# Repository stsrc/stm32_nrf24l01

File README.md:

# stm32_nrf24l01 - GPS localization project

Idea of this project is to create GPS localization system which utilises android
application to present distance and direction to the GPS receiver.

To achieve that multiple devices are used: on slave side we use NEO-6M GPS
module and nrf24l01 module to transmit GPS data to the master side.
On master side we use nrf24l01 to receive GPS data and HM-10 module to send it
to the android phone.

Android application is located in another repository: [whereIsCat](https://github.com/stsrc/whereIsCat)

## Repository content:

slave PCB with nrf24l01 transmitter and NEO-6M GPS receiver, battery powered

    ./src-kicad/stm32_slave_bat

slave firmware

    ./stm32f031f6_slave

master PCB with nrf24l01 receiver and HM-10 bluetooth transmitter, battery powered

    ./src-kicad/stm32_master_bt_bat

master firmware

    ./stm32f031f6_master

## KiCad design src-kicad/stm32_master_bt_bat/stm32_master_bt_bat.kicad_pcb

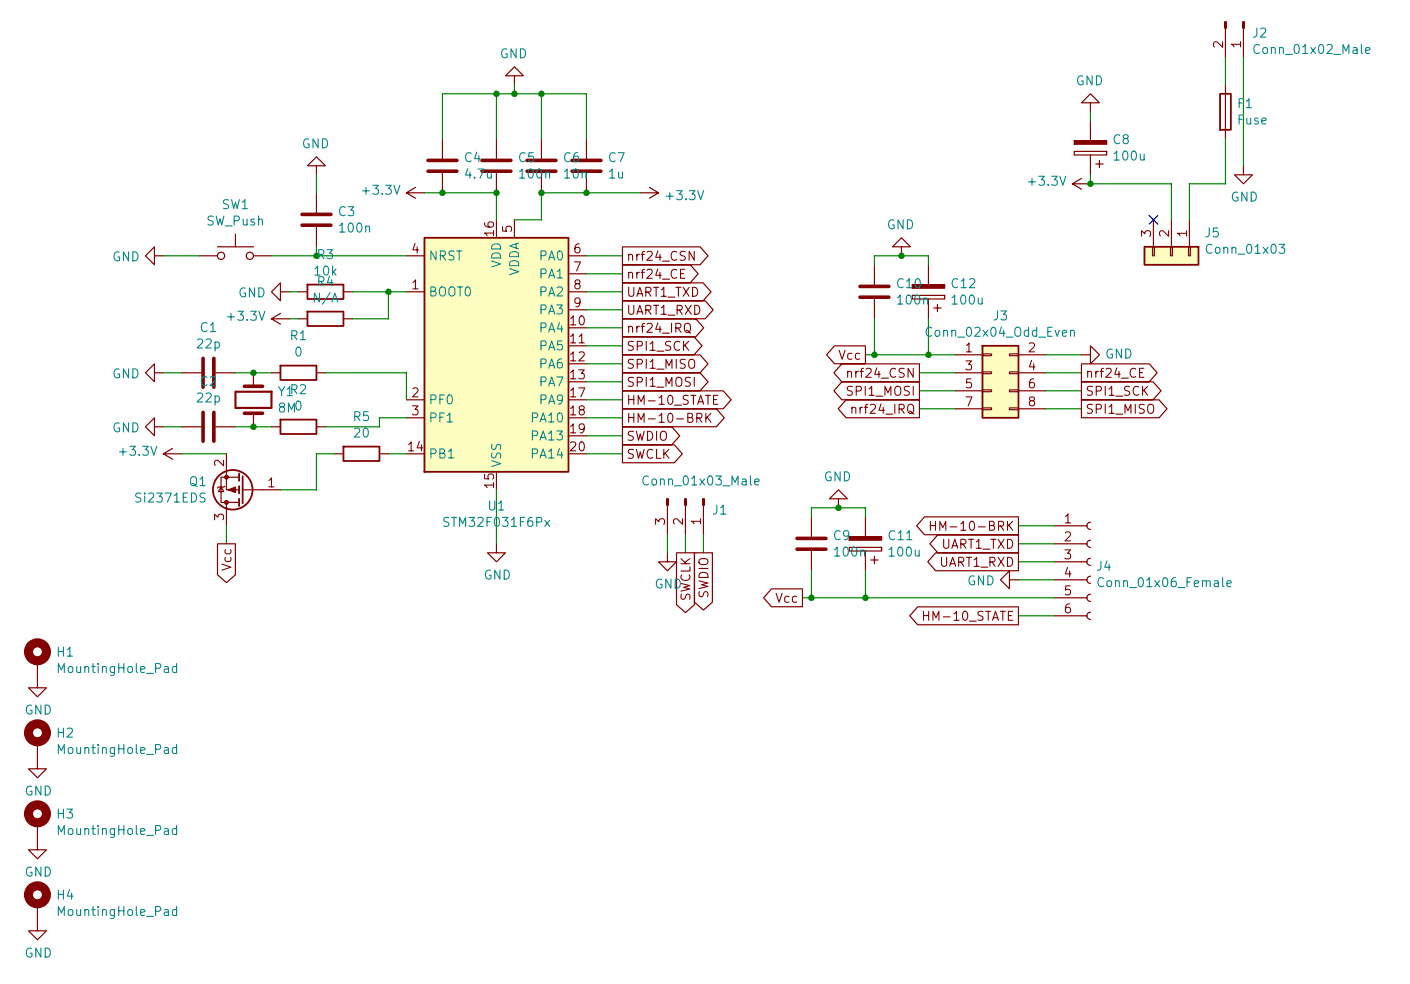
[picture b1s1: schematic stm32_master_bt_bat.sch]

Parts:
C1, C2: 22p; C_0805_2012Metric_Pad1.18x1.45mm_HandSolder
C3, C5, C9, C10: 100n; C_0805_2012Metric_Pad1.18x1.45mm_HandSolder
C4: 4.7u; C_0805_2012Metric_Pad1.18x1.45mm_HandSolder
C6: 10n; C_0805_2012Metric_Pad1.18x1.45mm_HandSolder
C7: 1u; C_0805_2012Metric_Pad1.18x1.45mm_HandSolder
C8, C11, C12: 100u; CP_Elec_6.3x5.8
F1: Fuse; smd-2410
H1, H2, H3, H4: MountingHole_Pad; MountingHole_3.2mm_M3_DIN965_Pad
J1: Conn_01x03_Male; PinHeader_1x03_P2.54mm_Vertical
J2: Conn_01x02_Male; PinHeader_1x02_P2.54mm_Vertical
J3: Conn_02x04_Odd_Even; PinSocket_2x04_P2.54mm_Vertical
J4: Conn_01x06_Female; PinSocket_1x06_P2.54mm_Vertical
J5: Conn_01x03; PRZELBL1X3
Q1: Si2371EDS; SOT-23
R1, R2: 0; R_0805_2012Metric_Pad1.20x1.40mm_HandSolder
R3: 10k; R_0805_2012Metric_Pad1.20x1.40mm_HandSolder
R4: N/A; R_0805_2012Metric_Pad1.20x1.40mm_HandSolder
R5: 20; R_0805_2012Metric_Pad1.20x1.40mm_HandSolder
SW1: SW_Push; SW_PUSH_6mm_H5mm
U1: STM32F031F6Px; TSSOP-20_4.4x6.5mm_P0.65mm
Y1: 8M; Crystal_SMD_HC49-SD

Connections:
+3V3: C4.2, C5.2, C6.1, C7.1, C8.1, J5.2, Q1.2 (S), R4.2, U1.5 (VDDA), U1.16 (VDD)
GND: C1.2, C2.2, C3.1, C4.1, C5.1, C6.2, C7.2, C8.2, C9.1, C10.1, C11.2, C12.2, H1.1, H2.1, H3.1, H4.1, J1.3, J2.1, J3.2, J4.4, R3.2, SW1.1, U1.15 (VSS)
HM-10-BRK: J4.1, U1.18 (PA10)
HM-10_STATE: J4.6, U1.17 (PA9)
unnamed: C1.1, R1.2, Y1.1
unnamed: C2.1, R2.2, Y1.2
unnamed: C3.2, SW1.2, U1.4 (NRST)
unnamed: F1.1, J2.2
unnamed: F1.2, J5.1
unnamed: Q1.1 (G), R5.2
unnamed: R1.1, U1.2 (PF0)
unnamed: R2.1, U1.3 (PF1)
unnamed: R3.1, R4.1, U1.1 (BOOT0)
unnamed: R5.1, U1.14 (PB1)
SPI1_MISO: J3.8, U1.12 (PA6)
SPI1_MOSI: J3.5, U1.13 (PA7)
SPI1_SCK: J3.6, U1.11 (PA5)
SWCLK: J1.2, U1.20 (PA14)
SWDIO: J1.1, U1.19 (PA13)
UART1_RXD: J4.3, U1.9 (PA3)
UART1_TXD: J4.2, U1.8 (PA2)
Vcc: C9.2, C10.2, C11.1, C12.1, J3.1, J4.5, Q1.3 (D)
nrf24_CE: J3.4, U1.7 (PA1)
nrf24_CSN: J3.3, U1.6 (PA0)
nrf24_IRQ: J3.7, U1.10 (PA4)

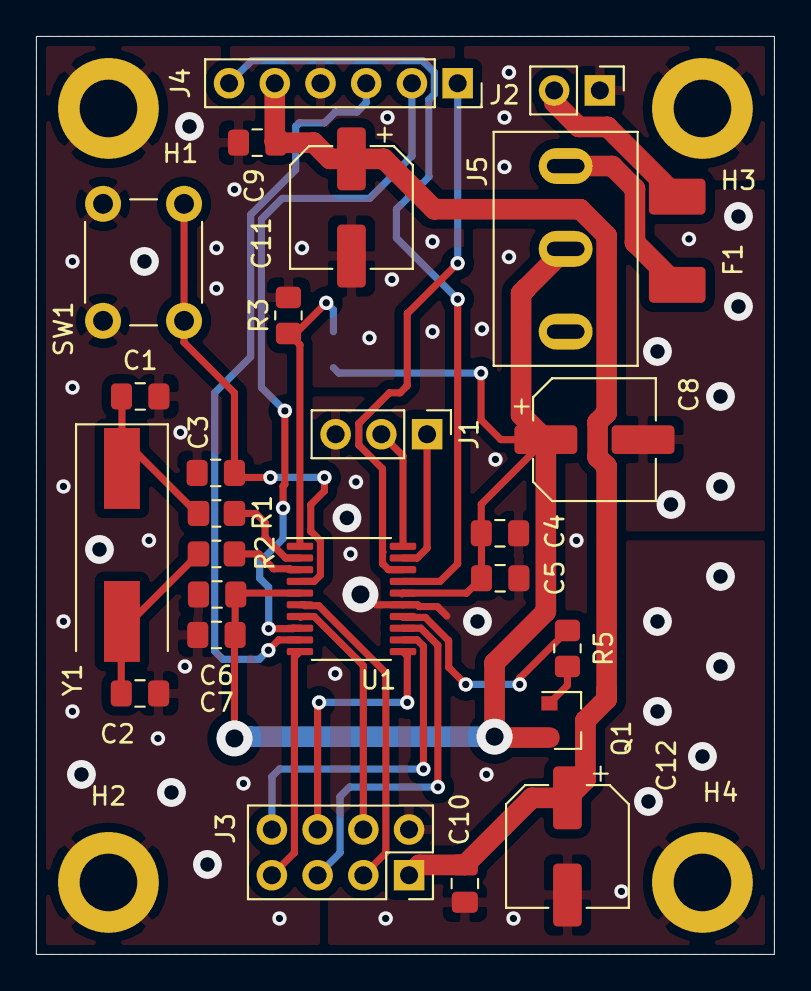
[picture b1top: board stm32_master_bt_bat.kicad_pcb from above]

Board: 2 copper layers, 41.0 x 51.0 mm, 31 parts (1 on the bottom side), 25 nets.

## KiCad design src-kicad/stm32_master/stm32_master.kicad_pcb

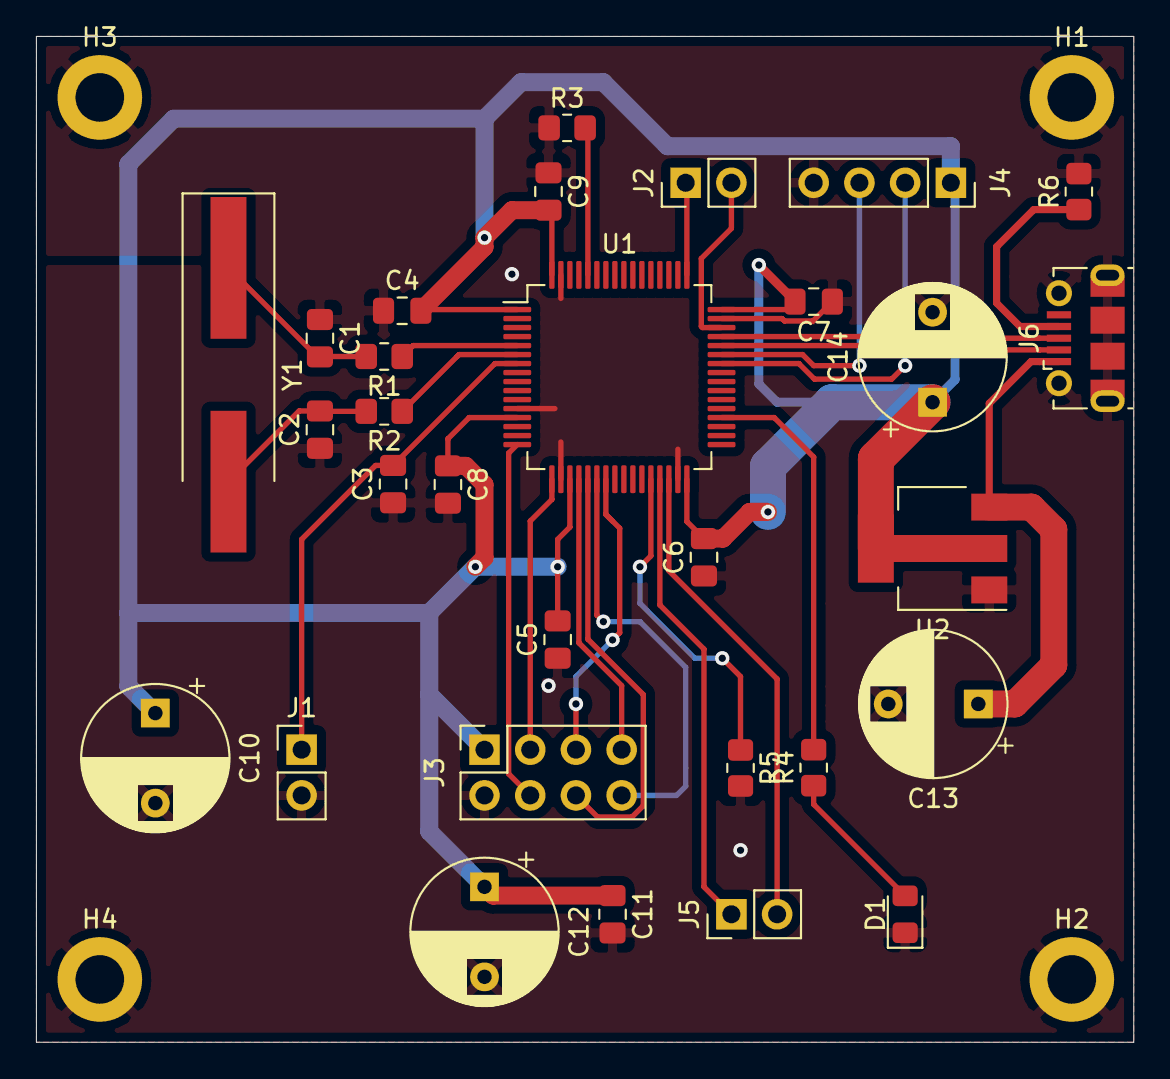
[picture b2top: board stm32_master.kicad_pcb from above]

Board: 2 copper layers, 61.0 x 55.9 mm, 34 parts (0 on the bottom side), 27 nets.

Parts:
C1, C2: 20p; C_0805_2012Metric_Pad1.18x1.45mm_HandSolder
C3, C4, C5, C6, C7, C9, C11: 100n; C_0805_2012Metric_Pad1.18x1.45mm_HandSolder
C8: 10n; C_0805_2012Metric_Pad1.18x1.45mm_HandSolder
C10: 1u; CP_Radial_D8.0mm_P5.00mm
C12, C14: 100u; CP_Radial_D8.0mm_P5.00mm
C13: 10u; CP_Radial_D8.0mm_P5.00mm
D1: LED; LED_0805_2012Metric_Pad1.15x1.40mm_HandSolder
H1, H2, H3, H4: MountingHole_Pad; MountingHole_2.7mm_M2.5_DIN965_Pad
J1, J2, J5: Conn_01x02_Male; PinHeader_1x02_P2.54mm_Vertical
J3: Conn_02x04_Odd_Even; PinSocket_2x04_P2.54mm_Vertical
J4: Conn_01x04; PinSocket_1x04_P2.54mm_Vertical
J6: USB_B_Micro; USB_Micro-B_Molex-105017-0001
R1: 0; R_0805_2012Metric_Pad1.20x1.40mm_HandSolder
R2: 220; R_0805_2012Metric_Pad1.20x1.40mm_HandSolder
R3, R5: 470; R_0805_2012Metric_Pad1.20x1.40mm_HandSolder
R4: 4.75; R_0805_2012Metric_Pad1.20x1.40mm_HandSolder
R6: N/A; R_0805_2012Metric_Pad1.20x1.40mm_HandSolder
U1: STM32F103RBTx; LQFP-64_10x10mm_P0.5mm
U2: LD1117S33TR_SOT223; SOT-223-3_TabPin2
Y1: Crystal; Crystal_SMD_HC49-SD_HandSoldering

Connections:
+3V3: C4.2, C5.2, C6.2, C7.2, C8.1, C9.2, C10.1, C11.1, C12.1, C14.1, J3.1, J4.1, U1.1, U1.13, U1.19, U1.32, U1.48, U1.64, U2.2
+5V: C13.1, J6.1, U2.3
BOOT1: R5.1, U1.28
GND: C1.1, C2.1, C3.1, C4.1, C5.1, C6.1, C7.1, C8.2, C9.1, C10.2, C11.2, C12.2, C13.2, C14.2, D1.1, H1.1, H2.1, H3.1, H4.1, J1.2, J3.2, J4.4, J6.5, J6.6, R3.1, R5.2, R6.2, U1.12, U1.18, U1.31, U1.47, U1.63, U2.1
unnamed: C1.2, R1.2, Y1.1
unnamed: C2.2, R2.2, Y1.2
unnamed: C3.2, J1.1, U1.7
unnamed: D1.2, R4.1
unnamed: J6.4, R6.1
unnamed: R1.1, U1.5
unnamed: R2.1, U1.6
unnamed: R3.2, U1.60
unnamed: R4.2, U1.36
SPI1_MISO: J3.8, U1.22
SPI1_MOSI: J3.5, U1.23
SPI1_SCK: J3.6, U1.21
SWCLK: J2.1, U1.49
SWDIO: J2.2, U1.46
USART1_RX: J4.3, U1.43
USART1_TX: J4.2, U1.42
USART3_RX: J5.2, U1.30
USART3_TX: J5.1, U1.29
USB_DM: J6.2, U1.44
USB_DP: J6.3, U1.45
nrf24_CE: J3.4, U1.16
nrf24_CSN: J3.3, U1.17
nrf24_IRQ: J3.7, U1.20

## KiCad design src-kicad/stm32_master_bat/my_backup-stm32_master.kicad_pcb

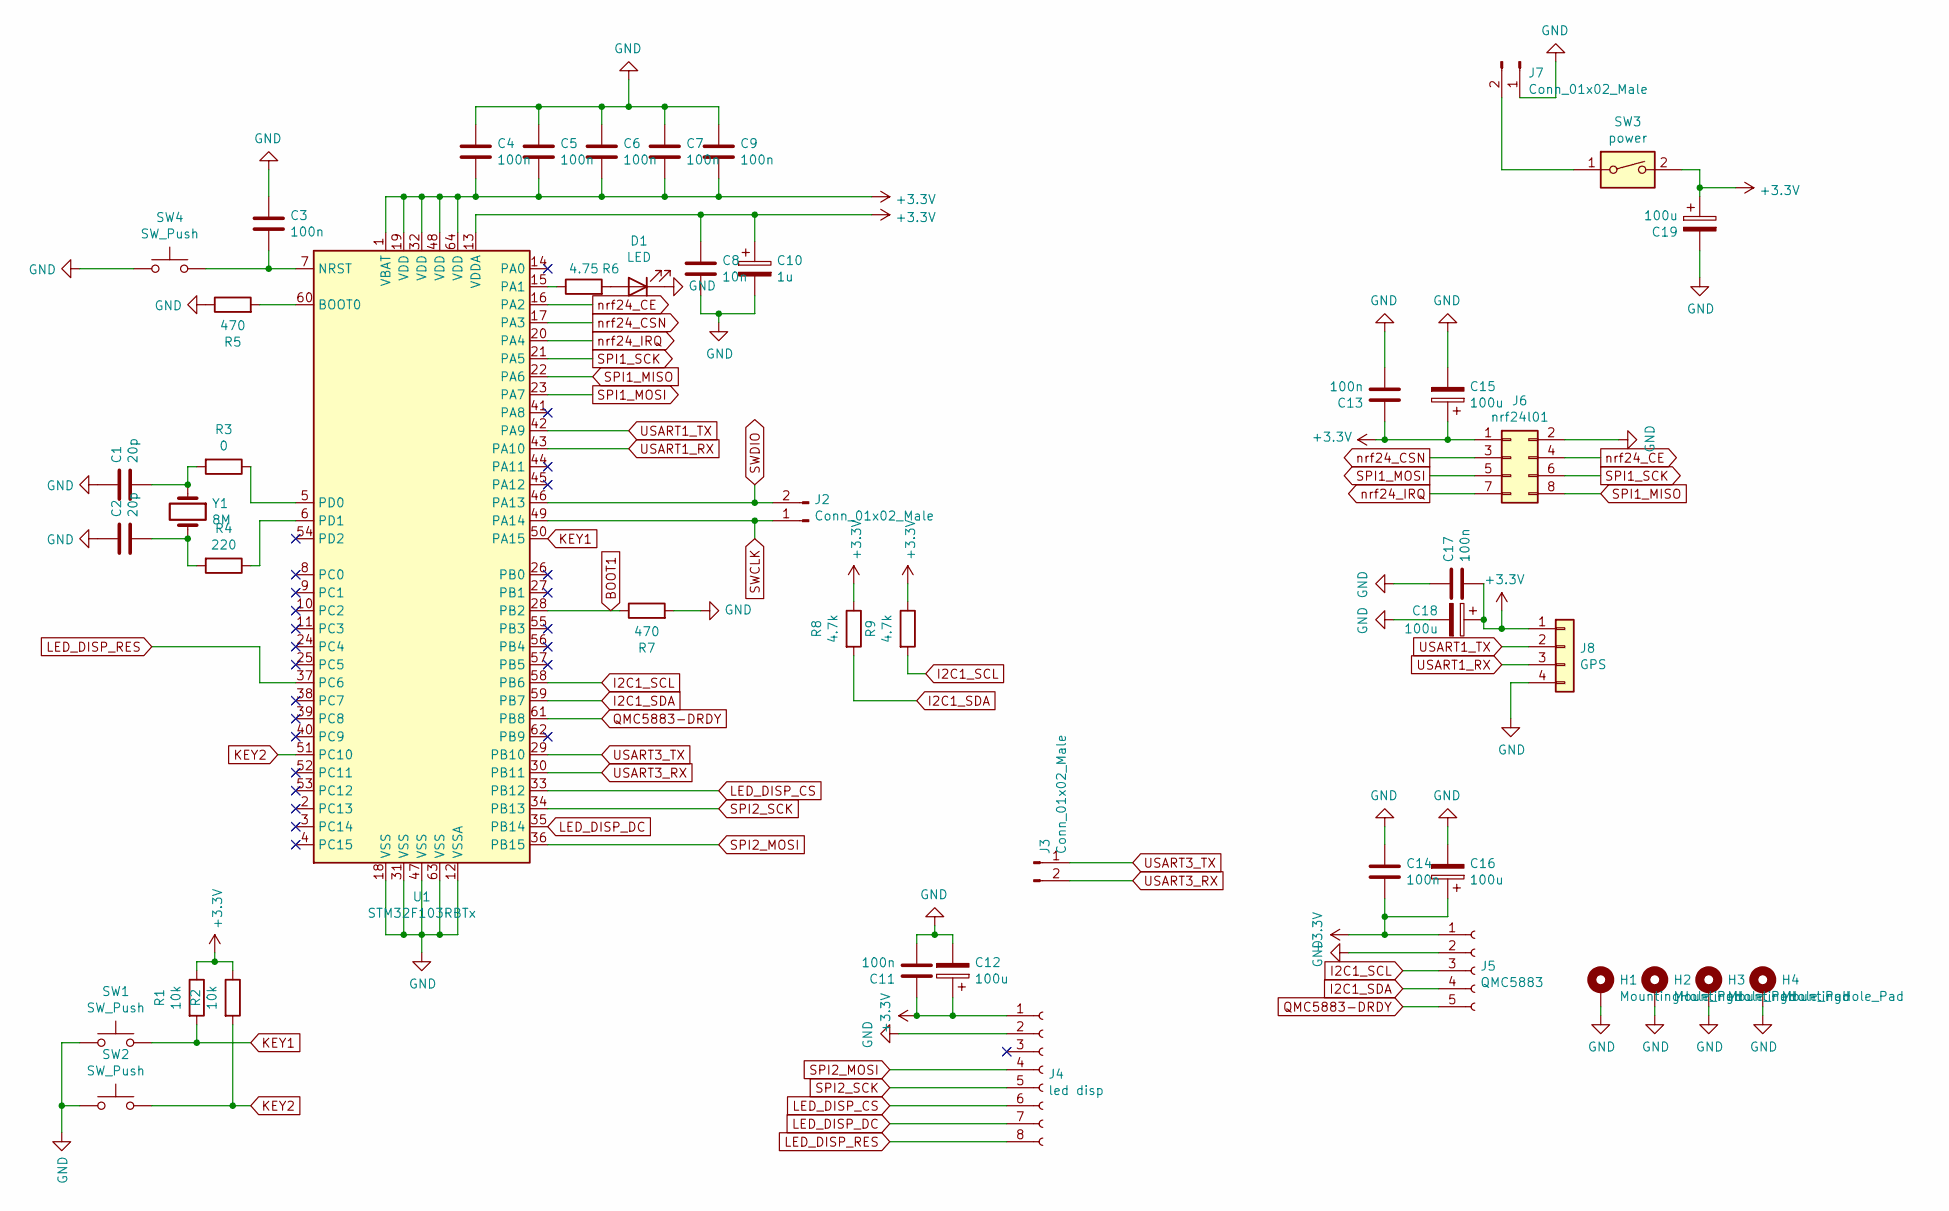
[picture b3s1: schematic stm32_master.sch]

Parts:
C1, C2: 20p; C_0805_2012Metric_Pad1.18x1.45mm_HandSolder
C3, C4, C5, C6, C7, C9, C11, C13, C14, C17: 100n; C_0805_2012Metric_Pad1.18x1.45mm_HandSolder
C8: 10n; C_0805_2012Metric_Pad1.18x1.45mm_HandSolder
C10: 1u; CP_Radial_D5.0mm_P2.50mm
C12, C15, C16, C18, C19: 100u; CP_Radial_D5.0mm_P2.50mm
D1: LED; LED_0805_2012Metric_Pad1.15x1.40mm_HandSolder
H1, H2, H3, H4: MountingHole_Pad; MountingHole_2.7mm_M2.5_DIN965_Pad
J2, J3, J7: Conn_01x02_Male; PinHeader_1x02_P2.54mm_Vertical
J4: led disp; PinSocket_1x08_P2.54mm_Vertical
J5: QMC5883; PinSocket_1x05_P2.54mm_Vertical
J6: nrf24l01; PinSocket_2x04_P2.54mm_Vertical
J8: GPS; PinSocket_1x04_P2.54mm_Vertical
R1, R2: 10k; R_0805_2012Metric_Pad1.20x1.40mm_HandSolder
R3: 0; R_0805_2012Metric_Pad1.20x1.40mm_HandSolder
R4: 220; R_0805_2012Metric_Pad1.20x1.40mm_HandSolder
R5, R7: 470; R_0805_2012Metric_Pad1.20x1.40mm_HandSolder
R6: 4.75; R_0805_2012Metric_Pad1.20x1.40mm_HandSolder
R8, R9: 4.7k; R_0805_2012Metric_Pad1.20x1.40mm_HandSolder
SW1, SW2, SW4: SW_Push; SW_PUSH_6mm_H5mm
SW3: power; SW_DIP_SPSTx01_Slide_6.7x4.1mm_W7.62mm_P2.54mm_LowProfile
U1: STM32F103RBTx; LQFP-64_10x10mm_P0.5mm
Y1: 8M; Crystal_SMD_HC49-SD_HandSoldering

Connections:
+3V3: C4.2, C5.2, C6.2, C7.2, C8.1, C9.2, C10.1, C11.1, C12.1, C13.1, C14.2, C15.1, C16.1, C17.2, C18.1, C19.1, J4.1, J5.1, J6.1, J8.1, R1.1, R2.1, R8.1, R9.1, SW3.2, U1.1 (VBAT), U1.13 (VDDA), U1.19 (VDD), U1.32 (VDD), U1.48 (VDD), U1.64 (VDD)
BOOT1: R7.1, U1.28 (PB2)
GND: C1.1, C2.1, C3.1, C4.1, C5.1, C6.1, C7.1, C8.2, C9.1, C10.2, C11.2, C12.2, C13.2, C14.1, C15.2, C16.2, C17.1, C18.2, C19.2, D1.1 (K), H1.1, H2.1, H3.1, H4.1, J4.2, J5.2, J6.2, J7.1, J8.4, R5.1, R7.2, SW1.1, SW2.1, SW4.1, U1.12 (VSSA), U1.18 (VSS), U1.31 (VSS), U1.47 (VSS), U1.63 (VSS)
I2C1_SCL: J5.3, R9.2, U1.58 (PB6)
I2C1_SDA: J5.4, R8.2, U1.59 (PB7)
KEY1: R1.2, SW1.2, U1.50 (PA15)
KEY2: R2.2, SW2.2, U1.51 (PC10)
LED_DISP_CS: J4.6, U1.33 (PB12)
LED_DISP_DC: J4.7, U1.35 (PB14)
LED_DISP_RES: J4.8, U1.37 (PC6)
unnamed: C1.2, R3.2, Y1.1
unnamed: C2.2, R4.2, Y1.2
unnamed: C3.2, SW4.2, U1.7 (NRST)
unnamed: D1.2 (A), R6.2
unnamed: J7.2, SW3.1
unnamed: R3.1, U1.5 (PD0)
unnamed: R4.1, U1.6 (PD1)
unnamed: R5.2, U1.60 (BOOT0)
unnamed: R6.1, U1.15 (PA1)
QMC5883-DRDY: J5.5, U1.61 (PB8)
SPI1_MISO: J6.8, U1.22 (PA6)
SPI1_MOSI: J6.5, U1.23 (PA7)
SPI1_SCK: J6.6, U1.21 (PA5)
SPI2_MOSI: J4.4, U1.36 (PB15)
SPI2_SCK: J4.5, U1.34 (PB13)
SWCLK: J2.1, U1.49 (PA14)
SWDIO: J2.2, U1.46 (PA13)
USART1_RX: J8.3, U1.43 (PA10)
USART1_TX: J8.2, U1.42 (PA9)
USART3_RX: J3.2, U1.30 (PB11)
USART3_TX: J3.1, U1.29 (PB10)
nrf24_CE: J6.4, U1.16 (PA2)
nrf24_CSN: J6.3, U1.17 (PA3)
nrf24_IRQ: J6.7, U1.20 (PA4)

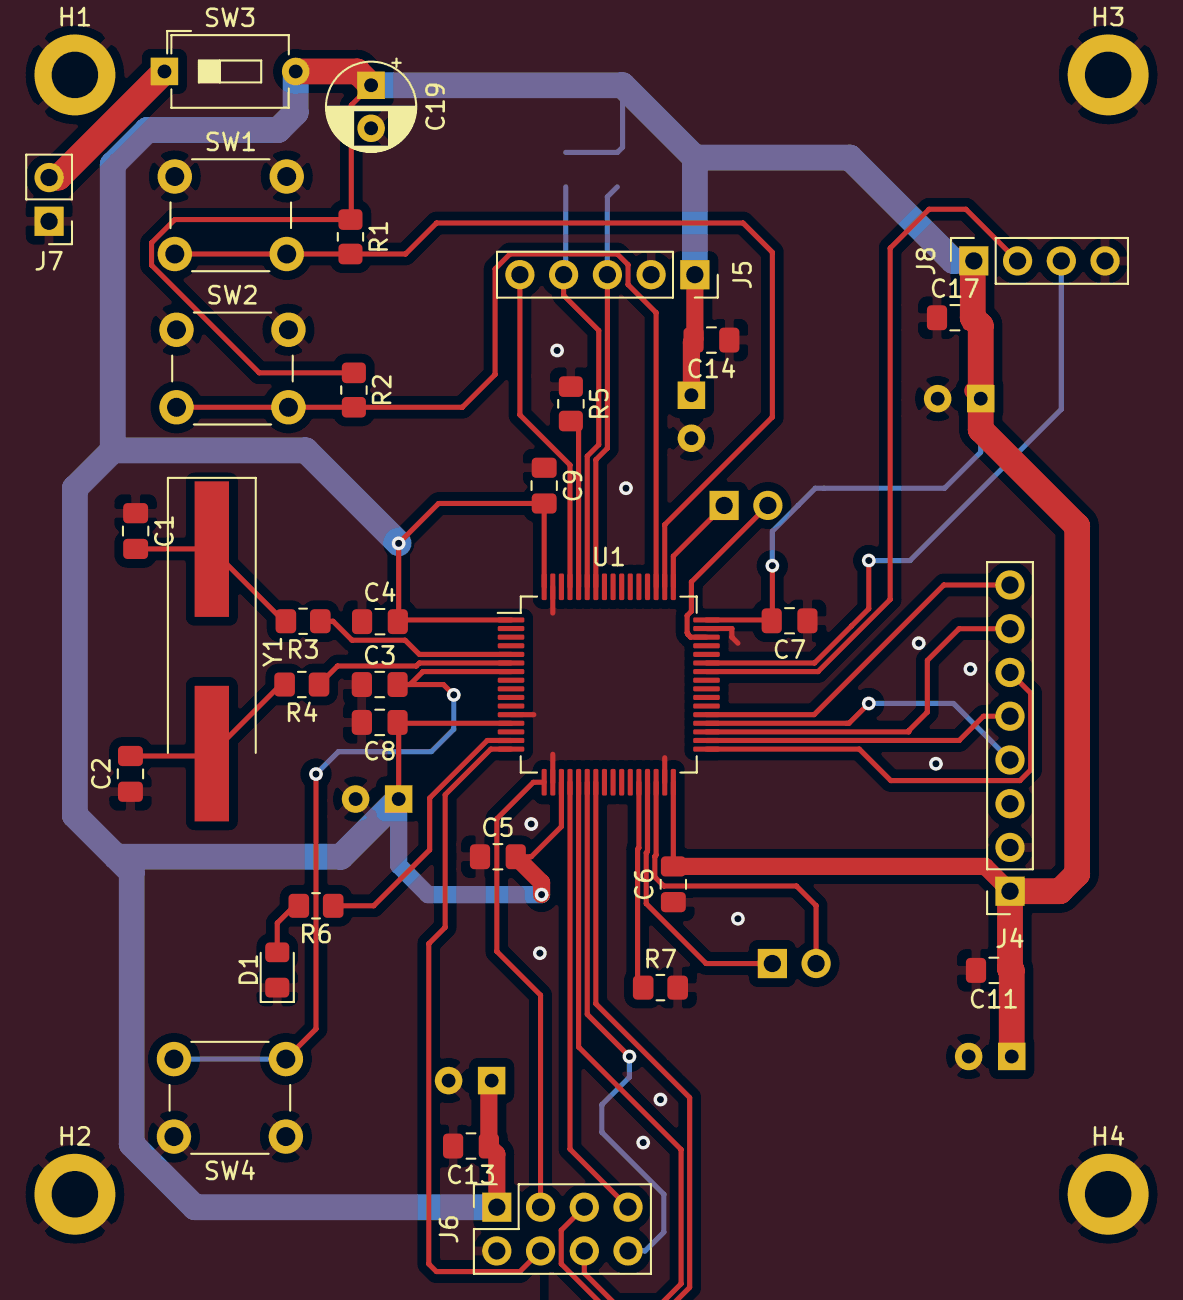
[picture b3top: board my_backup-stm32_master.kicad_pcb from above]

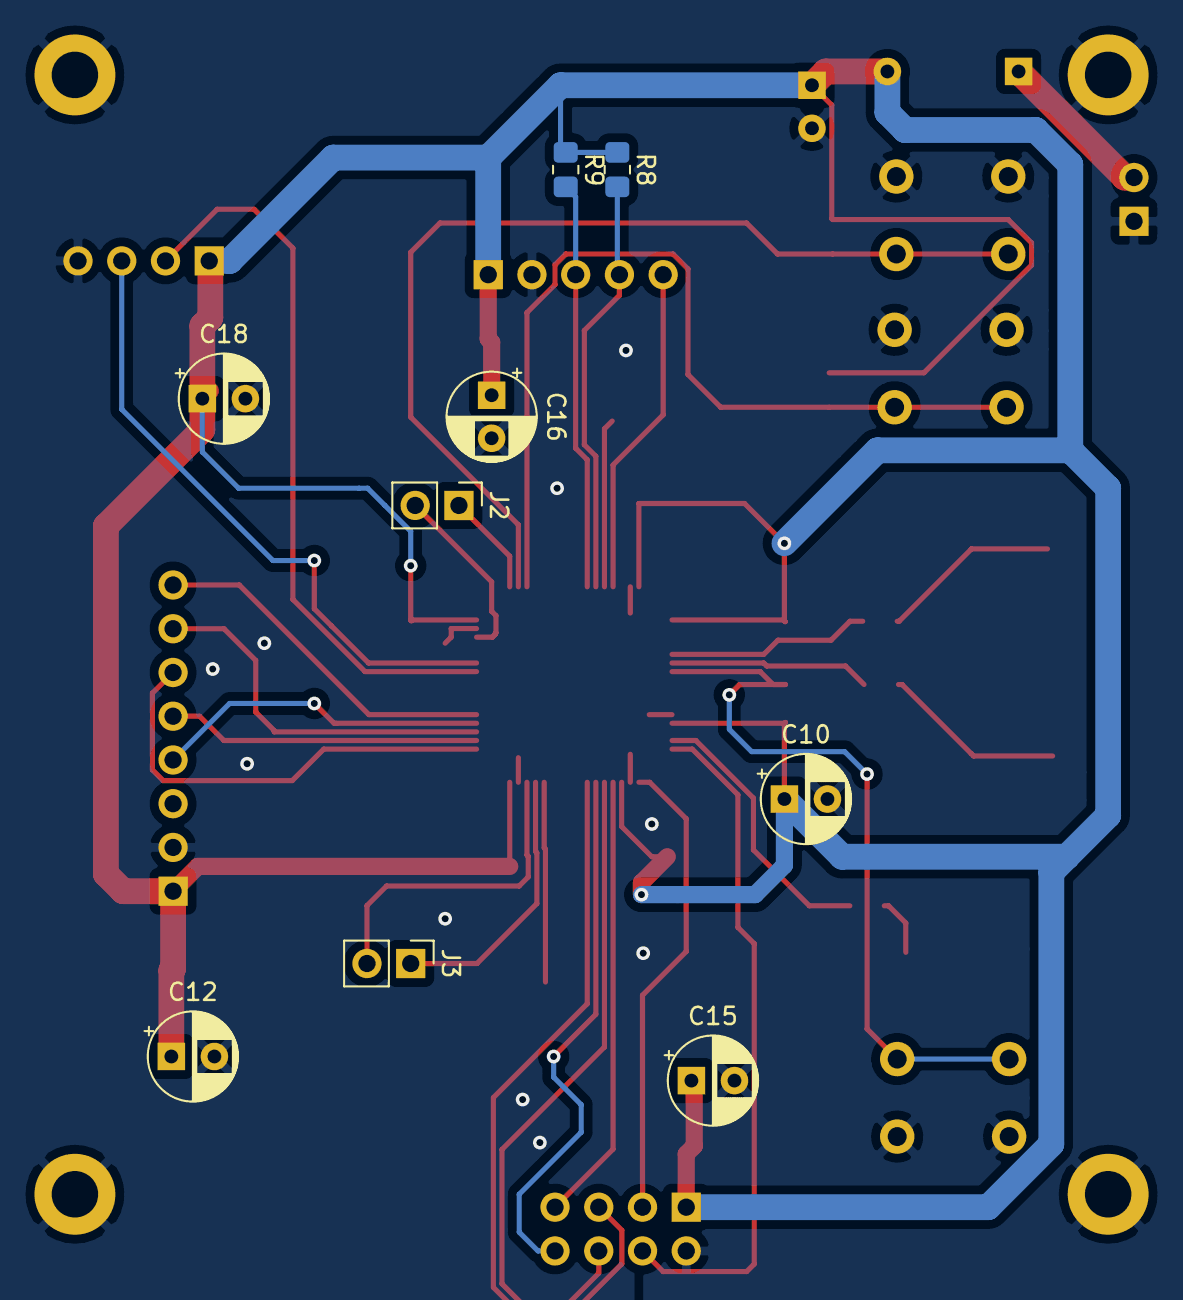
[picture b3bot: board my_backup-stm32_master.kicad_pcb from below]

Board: 2 copper layers, 46 parts (9 on the bottom side), 34 nets.

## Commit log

2020-12-19 Make SPI more generic
2020-12-19 Add .gitignore
2020-12-20 it works, but fails at 2 first commands...
2020-12-20 Small changes
2020-12-21 Preparing for irq
2020-12-21 irq works somehow
2020-12-21 Fix case with different sizeOfMessage
2020-12-21 set irq_flag when specific gpio is passed as argument
2020-12-30 add kicad project sources
2020-12-30 Change button shape
2020-12-31 Move stm32f100rb into seperate directory
2020-12-31 add stm32f031f6 directory
2020-12-31 Minor fixes in kicad
2021-02-06 Add slave/master directories
2021-02-06 update src-kicad directory (all files)
2021-02-06 move directories
2021-02-06 remove 'core' file
2021-02-06 Add license header to main.c
2021-02-06 make nrf24 up
2021-02-06 Add license
2021-02-06 Add license also to NRF24.h
2021-02-13 Add HAL_IncTick() into SysTick_Handler()
2021-02-13 Configure UART via registers not HAL function
2021-02-21 Temporary save of stm32f031f6_slave
2021-02-28 slave works
2021-03-26 Add , prefix to output from gps_get_data()
2021-03-26 Calculate USART1->BRR basing on SystemCoreClock
2021-03-26 Add setupClock() function; Use real gps data.
2021-03-26 Treat compilation warnings as errors
2021-03-26 Treat compialation warnings as errors in master also
2021-03-26 Add license, add clock_init() function, add overall code to main.c
2021-03-26 UART changes
2021-03-26 NRF24 changes
2021-03-26 Makefile changes
2021-03-27 Create LICENSE
2021-04-11 Add README.md. Remove old projects from src-kicad. Remove ignored code from stm32f031f6_master/src/NRF24.h
2021-04-11 Add space between # and header text
2021-04-11 README.md changes
2021-04-11 Add link to the android application repository
2021-04-11 Fix minor issues
2021-04-11 Fix readme
2021-05-01 Set nrf24l01 speed to 250kbps
2026-03-01 Use git submodules
    This commit introduces git submodules into this project - now Makefiles
    bases on them, not on local paths to libraries on hard drive, hence
    first build should be more smooth.
2026-03-01 Add simple_buffer_unittests.c
2026-03-01 Fix NRF24.c driver for slave device
    This commit fixes issue with one message being left on each loop
    iteration. It was caused by wrong order of setting/resseting csn and ce
    pins.
    Also delay_ms() were a little reworked.
2026-03-01 Refactor slave's SPI.c a little
2026-03-01 Change slave's main.c file format to unix
2026-03-01 One small change in stupid_delay.c
2026-03-01 Change fileformat of master's main.c to unix
2026-03-01 Simple refactor of master's SPI.c
2026-03-01 Few small changes in NRF24.*
2026-03-01 Small changes in stupid_delay.c
2026-03-01 Remove submodules from slave firmware directory
    Submodules are now located in the root in external diirectory
2026-03-01 Add slave's .gitignore
2026-03-01 Remove stm32f100rb code
    This code was needed only at the beggining
